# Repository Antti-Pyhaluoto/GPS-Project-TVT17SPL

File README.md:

# GPS Project 

Project for school application project.

Objective: Create a prototype of devices that sends data to database and can be controlled remotely from a web site. Create a website where data is visualized and deveice can be controlled.

Goal: GPS tracker that sends location data to database and a website that draws location data from database to map.

Additional goals: Drawing speed and distance traveled graphs from data and displaying live location data on website.

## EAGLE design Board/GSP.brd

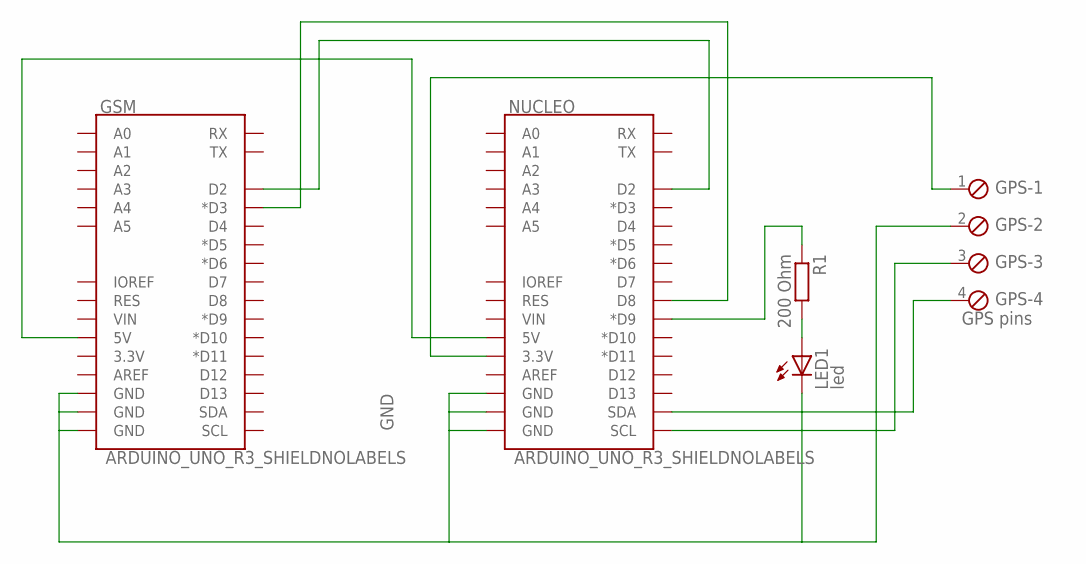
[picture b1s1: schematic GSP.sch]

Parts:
GPS: GPS pins; 4POL254
GSM: ARDUINO_UNO_R3_SHIELDNOLABELS; UNO_R3_SHIELD_NOLABELS
LED1: led; LED3MM
NUCLEO: ARDUINO_UNO_R3_SHIELDNOLABELS; UNO_R3_SHIELD_NOLABELS
R1: 200 Ohm; 0204/5

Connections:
GND: GPS.2, GSM.GND@0 (GND), GSM.GND@1 (GND), GSM.GND@2 (GND), LED1.K (C), NUCLEO.GND@0 (GND), NUCLEO.GND@1 (GND), NUCLEO.GND@2 (GND)
unnamed: GSM.5V, NUCLEO.5V
unnamed: NUCLEO.D9 (*D9), R1.1
unnamed: LED1.A, R1.2
unnamed: GPS.1, NUCLEO.3.3V
unnamed: GSM.D2, NUCLEO.D2
unnamed: GSM.D3 (*D3), NUCLEO.D8
unnamed: GPS.4, NUCLEO.SDA
unnamed: GPS.3, NUCLEO.SCL

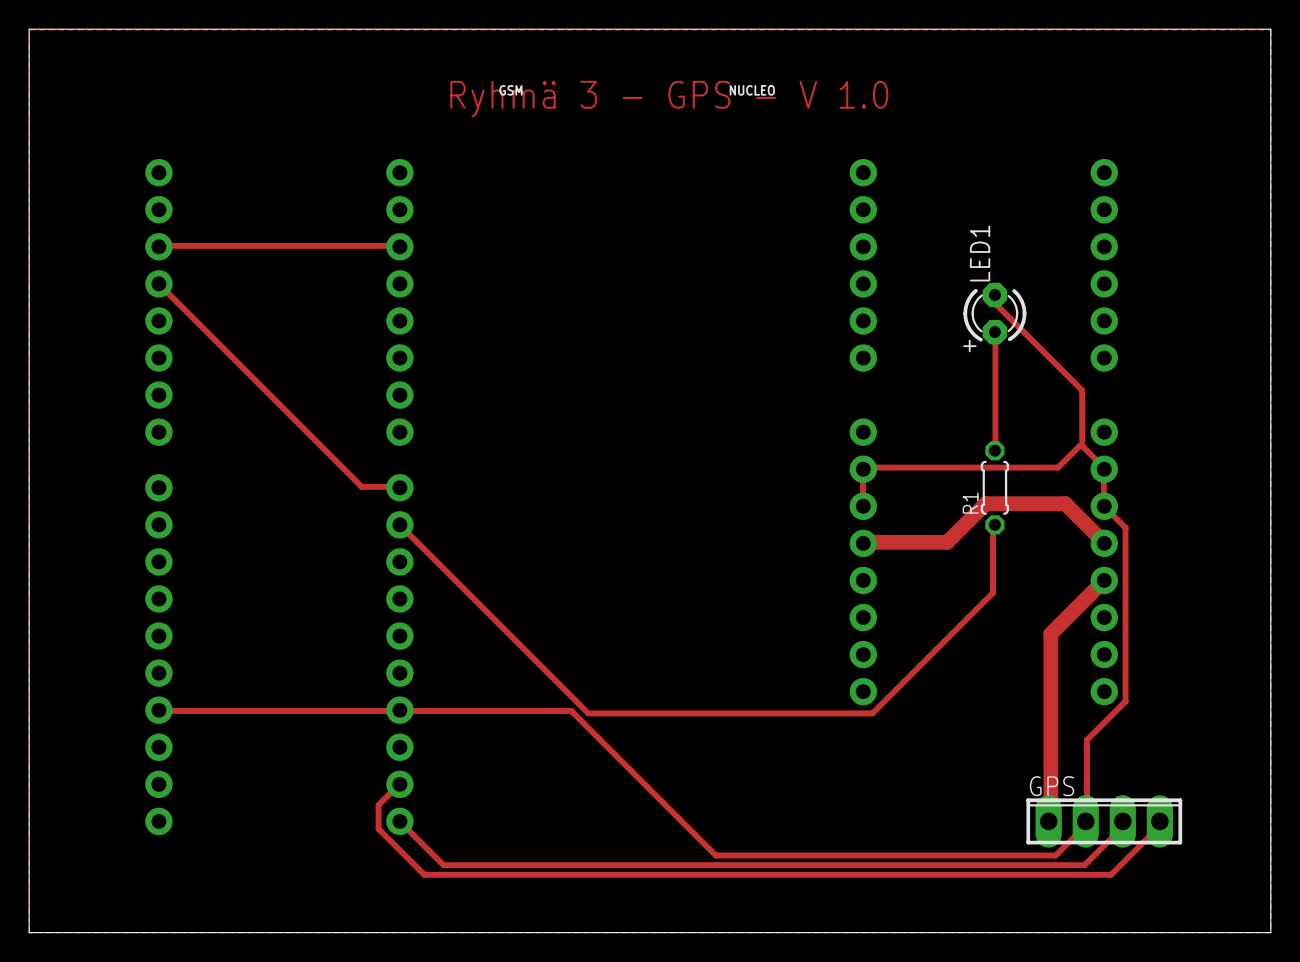
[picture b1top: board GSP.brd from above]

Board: 2 copper layers, 85.1 x 61.9 mm, 5 parts (0 on the bottom side), 9 nets.

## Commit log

2018-11-01 Added folder for individual aspects
2018-11-06 GSM serial pass
2018-11-06 Removed useless files
2018-11-07 Added new server code.
2018-11-09 New main that autmotically issues AT commands needed for GPRS TCP/IP communication.
2018-11-12 Improved autmatic setup and added automatic TCP/IP connection for testing.
2018-11-12 Web code test for drawing a line on map
2018-11-13 Draws a line based on array of location points.
2018-11-15 GPS raw data parsing improved.
2018-11-15 Added ability to send variables with HTTP.
2018-11-16 Final version, without comments
2018-11-16 Minor changes to gsm code and beginning of the future web code.
2018-11-19 Added security/filtering for the input values
2018-11-20 Changed serial pins
2018-11-20 Added selecting route from dropdown box and centering view to the middle of the route.
2018-11-20 Added selecting route from dropdown box and centering view to the middle of the route. Added forgotten quotemarks.
2018-11-20 Fixed quotemarks.
2018-11-20 PCB board files added.
2018-11-21 Sending of data to server.
2018-11-21 Updated board. Test of webpage.
2018-11-22 Added first draft of combined GPS/GSM file.
2018-11-22 Added one line.
2018-11-22 Added chart that displays distance traveled.
2018-11-22 Speed chart displays speed according to place and time differences.
2018-11-26 Added view that displays the most recent location on map and updates it every 5 seconds.
2018-11-26 Added additional comments.
2018-11-26 Added forgotten file.
2018-11-26 New gps code.
2018-11-26 'uusi'
2018-11-26 Some changes.
2018-11-26 Resolved conflicts for real.
2018-11-26 Conitued combination.
2018-11-27 Added functionality of sending data to server. Improved startup.
2018-11-27 GPS data filtering improved
2018-11-27 GPS data filtering improved_version2
2018-11-27 Added led to idicate sending of location data.
2018-11-29 Changed floats to double. Changed char array sizes.
2018-11-29 Added update frequency functionality. Removed printing of AT commands.
2018-11-29 Added description of routes. Started the frequency management on web site.
2018-11-30 Added functionality of changing update frequency. Improved functionality.
2018-11-30 Added changing of update frequency to the website. Added newlines to end of files.
2018-12-03 Added markers to map to show timestamps for route.
2018-12-04 Recieving .php script updated and comments have been added
2018-12-10 Fixed speed calculation. Changed database from testi to Oikea.
2018-12-14 Changed language to English. Final.
2018-12-28 Update README.md
    Added better description of the project.

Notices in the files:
parts and their libraries:
SparkFun-Boards: Licensing: Creative Commons ShareAlike 4.0 International - https://creativecommons.org/licenses/by-sa/4.0
